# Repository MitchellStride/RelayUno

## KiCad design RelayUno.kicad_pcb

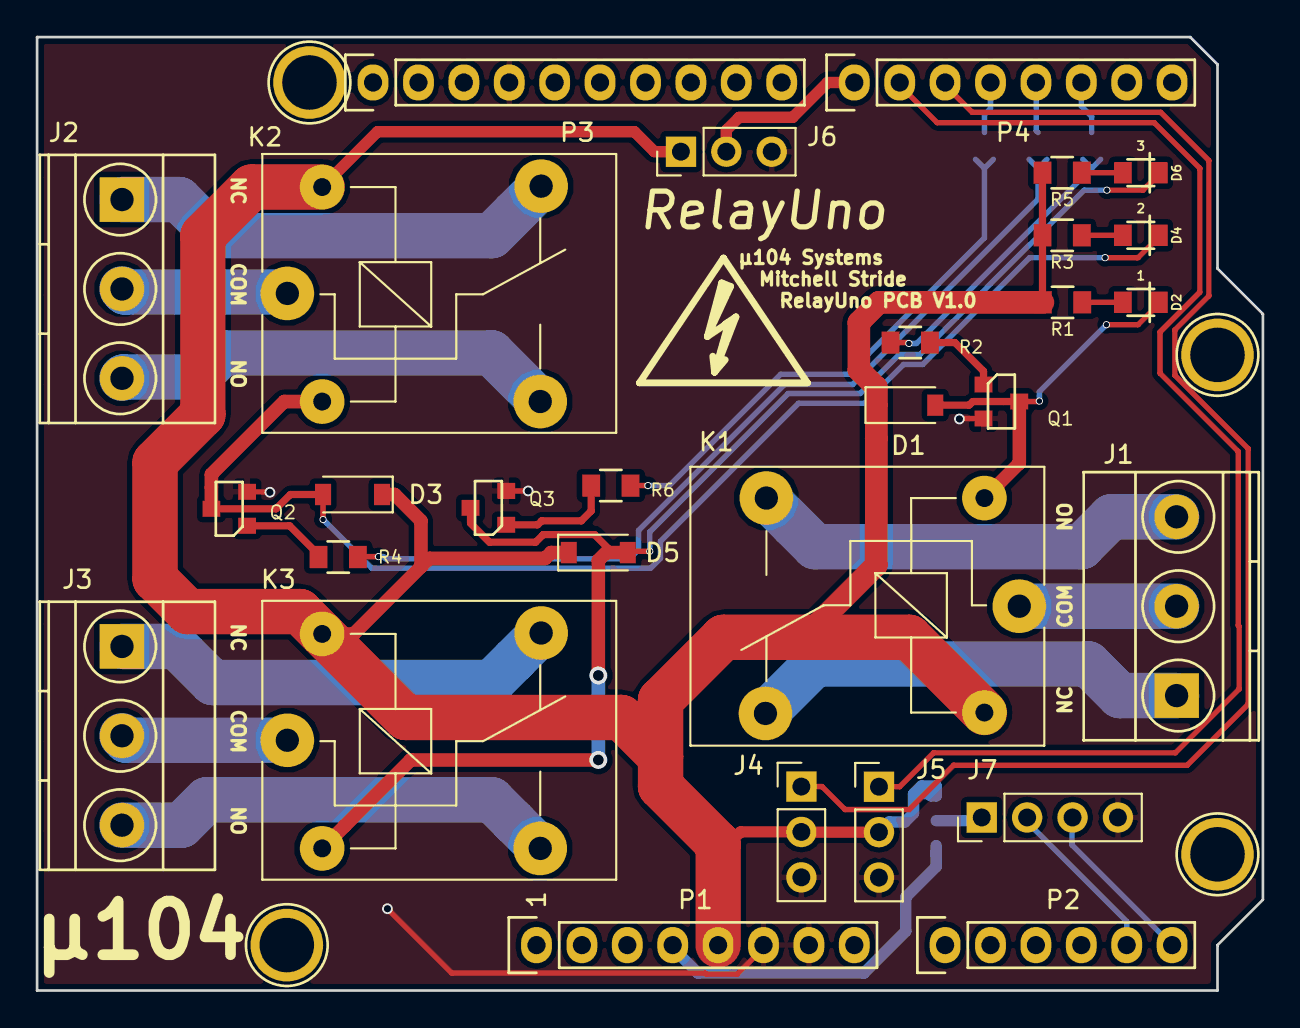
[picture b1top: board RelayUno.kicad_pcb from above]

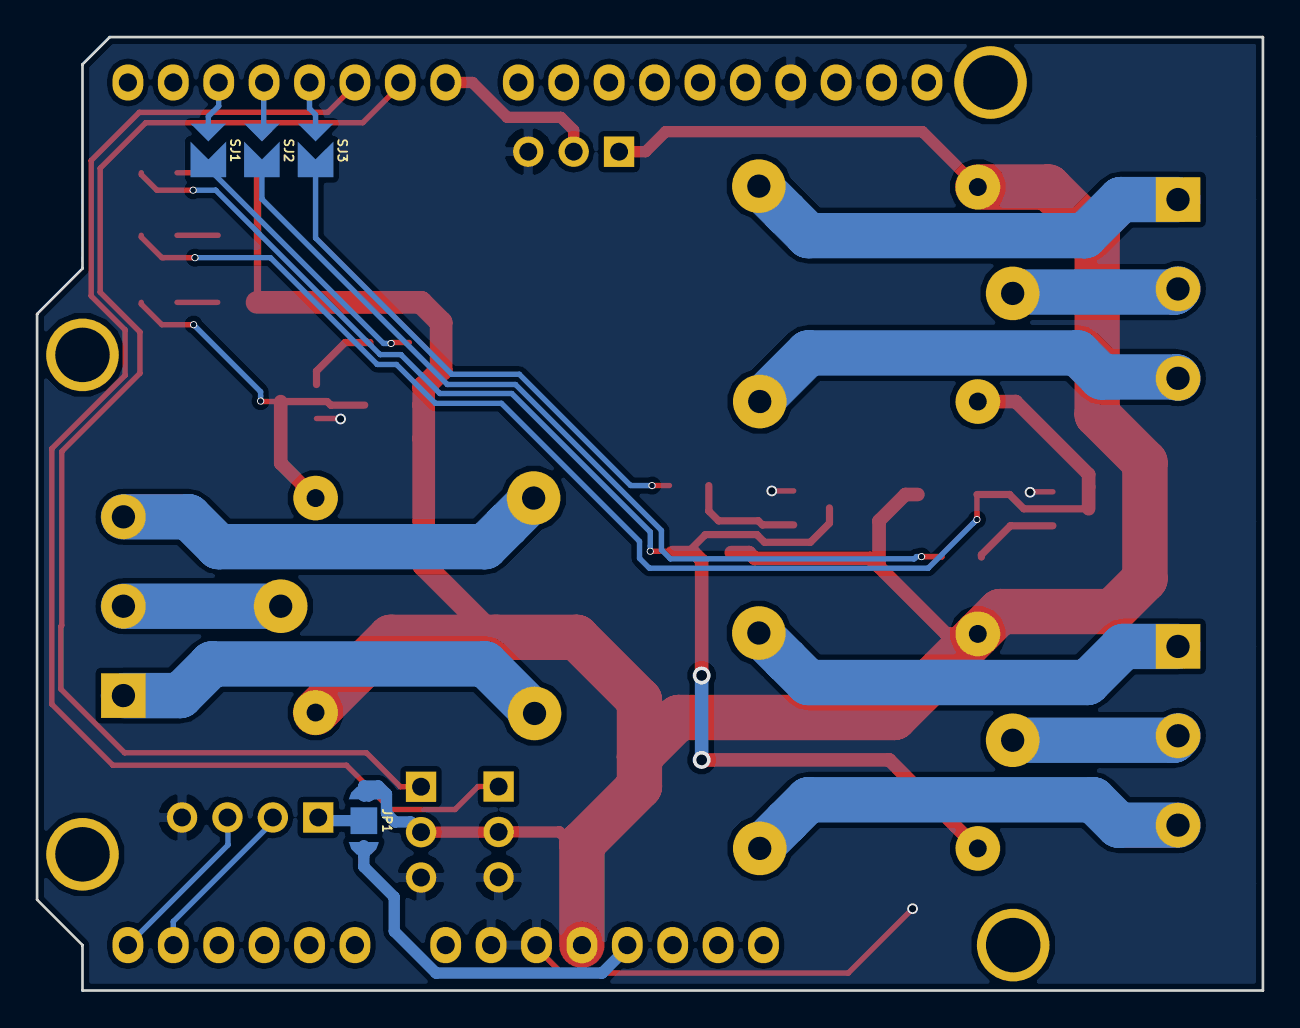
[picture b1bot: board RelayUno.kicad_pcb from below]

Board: 2 copper layers, 68.6 x 53.3 mm, 38 parts (4 on the bottom side), 33 nets.

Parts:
D1, D3, D5: D; D_SOD-123
D2: 1; LED_Wurth_WL-SMCW_0805_G
D4: 2; LED_Wurth_WL-SMCW_0805_G
D6: 3; LED_Wurth_WL-SMCW_0805_G
J1, J2, J3: Screw_Terminal_01x03; TerminalBlock_Phoenix_MKDS1.5-3pol
J4: SERVO1; Pin_Header_Straight_1x03_Pitch2.54mm
J5: SERVO2; Pin_Header_Straight_1x03_Pitch2.54mm
J6: DEVICE; Pin_Header_Straight_1x03_Pitch2.54mm
J7: I2C; Pin_Header_Straight_1x04_Pitch2.54mm
JP1: Jumper_NC_Dual; Jumper_EGG_2way
K1, K2, K3: SONGLE_SPDT; Relay_SPDT_SANYOU_SRD_Series_Form_C
P1: Power; Socket_Strip_Arduino_1x08
P2: Analog; Socket_Strip_Arduino_1x06
P3: Digital; Socket_Strip_Arduino_1x10
P4: Digital; Socket_Strip_Arduino_1x08
P5, P6, P7, P8: CONN_01X01; Arduino_1pin
Q1, Q2, Q3: Q_NPN_BCE; SOT-23-3
R1, R2, R3, R4, R5, R6: 1k; SMD_pkg_0805
SJ1, SJ2, SJ3: SolderJumper; solderBridge
logo1: Logo; Symbol_HighVoltage_Type2_SilkTop_VerySmall

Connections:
+3V3: JP1.3, P1.4
+5V: D1.1, D3.1, D5.1, J4.2, J5.2, J6.1, JP1.1, K1.5, K2.5, K3.5, P1.5, R1.2, R3.2, R5.2
/2: P4.6, SJ1.1
/3(**): P4.5, SJ2.1
/4: P4.4, SJ3.1
/5(**): J4.1, P4.3
/6(**): J5.1, P4.2
/7: J6.2, P4.1
/A4(SDA): J7.2, P2.5
/A5(SCL): J7.3, P2.6
/COM1: J1.2, K1.1
/COM2: J2.2, K2.1
/COM3: J3.2, K3.1
/NC1: J1.1, K1.4
/NC2: J2.1, K2.4
/NC3: J3.1, K3.4
/NO1: J1.3, K1.3
/NO2: J2.3, K2.3
/NO3: J3.3, K3.3
/relay1: R2.2, SJ1.2
/relay2: R4.2, SJ2.2
/relay3: R6.2, SJ3.2
GND: J4.3, J5.3, J6.3, J7.4, P1.6, P1.7, P3.4, Q1.2, Q2.2, Q3.2
unnamed: D1.2, D2.1, K1.2, Q1.3
unnamed: D2.2, R1.1
unnamed: D3.2, D4.1, K2.2, Q2.3
unnamed: D4.2, R3.1
unnamed: D5.2, D6.1, K3.2, Q3.3
unnamed: D6.2, R5.1
unnamed: J7.1, JP1.2
unnamed: Q1.1, R2.1
unnamed: Q2.1, R4.1
unnamed: Q3.1, R6.1

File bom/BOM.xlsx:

Component | Description | Part | References | Value | Footprint | Quantity Per PCB | Datasheet
1 | LED generic | LED | D2 | 1 | LED_Wurth_WL-SMCW_0805_G | 1 | 732-4986-1-ND
2 | LED generic | LED | D4 | 2 | LED_Wurth_WL-SMCW_0805_G | 1 | 732-4986-1-ND
3 | LED generic | LED | D6 | 3 | LED_Wurth_WL-SMCW_0805_G | 1 | 732-4986-1-ND
4 | Diode | D | D1 D3 D5 | D | D_SOD-123 | 3 | BAV21W-FDICT-ND
5 | Generic screw terminal, single row, 01x03 | Screw_Terminal_01x03 | J1 J2 J3 | Screw_Terminal_01x03 | TerminalBlock_Phoenix_MKDS1.5-3pol | 3 | ED2610-ND
12 | Transistor NPN (general) | Q_NPN_BEC | Q1 Q2 Q3 | Q_NPN_BCE | SOT-23-3 | 3 | MMBT3904-FDICT-ND
13 | Resistor | R | R1 R2 R3 R4 R5 R6 | 1k | SMD_pkg_0805 | 6 | RR12P1.0KDCT-ND
Component Groups: | 15
Component Count: | 33
Fitted Components: | 33
Number of PCBs: | 1
Total components: | 33
Schematic Version:
Schematic Date: | lun. 30 mars 2015
BoM Date: | 9/29/2018 4:13:31 PM
Schematic Source: | C:\projects\RelayUno\RelayUno.sch
KiCad Version: | Eeschema 4.0.7

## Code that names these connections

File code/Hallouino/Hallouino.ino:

/*******************************************
   Halloween Spoopy Skeleton Scares
     -Arduino Uno using custom RelayUno PCB
 ******************************************/
#include <Servo.h>

Servo zAxis;
Servo yTilt;

//Setup Peripherals
#define Relay1 2
#define Relay2 3
#define Relay3 4
#define Servo1 5
#define Servo2 6
#define PIR 7

int motion = 0;
int

unsigned long Time = 0;
unsigned long prevTime = 0;

void setup() {
  Serial.begin(9600);
  
  pinMode(LED_BUILTIN, OUTPUT);
  pinMode(Relay1, OUTPUT);
  pinMode(Relay2, OUTPUT);
  pinMode(Relay3, OUTPUT);
  pinMode(PIR, INPUT);
  zAxis.attach(Servo1);
  yTilt.attach(Servo2);
  yTilt.write(0);
  Serial.println("Started!");
}

void loop() {
  if ((millis() - prevTime) > 10000) {
    Serial.println("Ready for Scare!");
    waitMotion();
  }
}

void waitMotion() {
  while (1) {
    motion = digitalRead(PIR);
    if (motion) {
      Serial.println("Motion Detected - Start Scare!");
      prevTime = millis(); //Reset time stamp upon triggering SPOOK
      digitalWrite(LED_BUILTIN, HIGH);
      SPOOK();             //Scare Action Function
      return;
    }
  }
}

void SPOOK() {
  //Servo Triggering
  yTilt.write(90);
  delay(1000);
  for(int i = 89; i > 3; i--){
    yTilt.write(i);
    delay(30);
  }
  
  
  /* 
  //Relay Triggering
  digitalWrite(Relay1 = 1);
  delay(25);
  digitalWrite(Relay1 = 0);
  */
   Serial.println("Scare Done!");
   digitalWrite(LED_BUILTIN, LOW);
}

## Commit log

2018-09-29 Added ordered gerbers v1.0
2018-09-30 added untested code
2018-09-30 proto code with working wait to scare and spook function
2018-10-11 added some pics, only final code leftdsadsa
2018-10-11 added some pics, only final code left
